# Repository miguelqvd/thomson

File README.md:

# thomson

This repo holds tools and software I write (or gather) for Thomson computers.
These were designed and built by the French company Thomson in 1982-1986, and there is a small community
of enthusisats around them.

I write tools for cross-development as well as some scene demos. There may someday be games or native tools
as well. Occasionally I hack on hardware expansions.

Be sure to visit my wiki for technical information: http://pulkomandy.tk/wiki/

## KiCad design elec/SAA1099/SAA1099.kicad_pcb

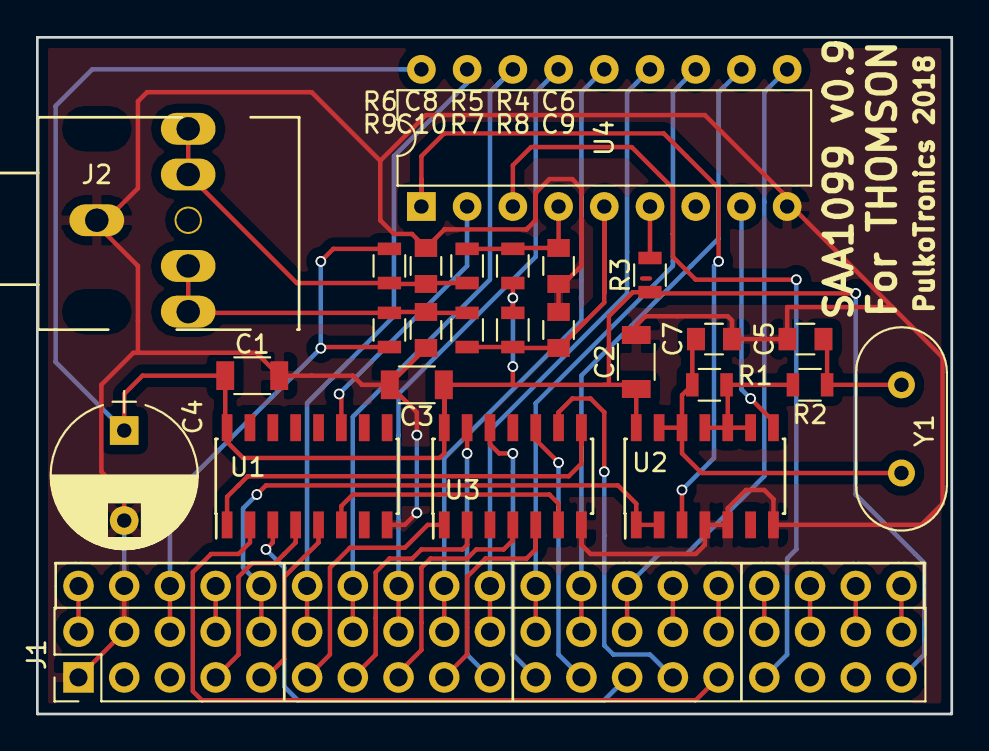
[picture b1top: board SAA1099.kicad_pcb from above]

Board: 2 copper layers, 50.8 x 37.6 mm, 26 parts (0 on the bottom side), 38 nets.

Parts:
C1, C2, C3: C; C_1206
C4: CP; CP_Radial_D8.0mm_P5.00mm
C5: 47pF; C_0805
C6, C8, C9, C10: 5nF; C_0805
C7: 33pF; C_0805
J1: Conn_02x19_Row_Letter_First; he902-he10-2x19
J2: Audio-Jack-3_2Switches; Jack_Stereo
R1: 5M; R_0805
R2: 6R; R_0805
R3, R5, R6, R8, R9: 10K; R_0805
R4, R7: 820; R_0805
U1: 74LS138; SOIC-16_3.9x9.9mm_Pitch1.27mm
U2: 74LS00; SOIC-14_3.9x8.7mm_Pitch1.27mm
U3: 74LS21; SOIC-14_3.9x8.7mm_Pitch1.27mm
U4: SAA1099; DIP-18_W7.62mm
Y1: Crystal; Crystal_HC18-U_Vertical

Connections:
//Axxx: J1.a4, U1.4
//CS: U1.11, U4.2
//WR: U2.3, U4.1
/A0: J1.a16, U4.3
/A1: J1.a15, U1.2
/A2: J1.a14, U3.9
/A3: J1.a13, U1.3
/A4: J1.a12, U3.10
/A5: J1.a11, U3.12
/A6: J1.a10, U3.13
/A7: J1.a9, U3.5
/A8: J1.a8, U3.4
/A9: J1.a7, U3.2
/A10: J1.a6, U3.1
/A11: J1.a5, U1.5
/CLK: U2.8, U4.8
/D0: J1.b13, U4.10
/D1: J1.b12, U4.11
/D2: J1.b11, U4.12
/D3: J1.b10, U4.13
/D4: J1.b9, U4.14
/D5: J1.b8, U4.15
/D6: J1.b7, U4.16
/D7: J1.b6, U4.17
/E: J1.b5, U2.1, U2.2
/Iref: R3.2, U4.6
/LINEL: C10.1, J2.2, J2.5, R8.1, R9.2
/LINER: C8.1, J2.1, J2.4, R5.1, R6.2
/OUTL: C9.1, R7.2, R8.2, U4.5
/OUTR: C6.1, R4.2, R5.2, U4.4
/SON: J1.b3, R6.1, R9.1
GND: C1.2, C2.2, C3.2, C4.2, C5.2, C6.2, C7.2, C8.2, C9.2, C10.2, J1.a1, J1.b2, J2.3, U1.8, U2.4, U2.5, U2.7, U3.7, U4.9
unnamed: C5.1, R2.1, Y1.1
unnamed: C7.1, R1.2, U2.12, U2.13, Y1.2
unnamed: R1.1, R2.2, U2.9, U2.10, U2.11
unnamed: U1.1, U3.8
unnamed: U1.6, U3.6
VCC: C1.1, C2.1, C3.1, C4.1, J1.a19, R3.1, R4.1, R7.1, U1.16, U2.14, U3.14, U4.18

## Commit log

2012-01-01 Add Memo5+.
2012-01-01 Remove useless files
2012-01-02 Add WIP HxC host software for Thomson computers. Not working yet because of timing problems...
2012-01-03 * Add re-routing of megarom (not finished!!) * Add MEMO7 connector to Thomson components library.
2012-01-04 Fix reset circuit Finish routing...
2012-01-15 Add host software for CrO2 (WIP)
2012-01-15 Load data from K7 file.
2012-01-16 Add motor on detection.
2012-01-17 * cross platform makefile * rename main file and executable
2012-01-24 WIP GUI
2012-01-24 C++ refactoring : move USB communication to device class.
2012-01-28 * Poll motor on pin status and report it in the GUI. * Some cleanup of device class.
2012-01-29 * Move GUI in its own class * Design C++ callbacksystem for IUP * Load file from menu
2012-01-29 Final version (?) of iup++, which handles callbacks with arguments. Needs C++11.
2012-02-03 Cleanup.
2012-02-04 WIP explorer * Fill in the block list * HexEditor in progress.
    Commiting because I'm trying to improve iupplusplus and want to make sure I can revert it if I fail.
2012-02-05 * Support for ZX spectrup TAP files.
2012-03-10 work in progress write support. * With latest beta firmware there is no spinup problem anymore in direct access mode, * Read the CFG file and display settings menu * Save settings (not perfectly work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
2012-03-10 More work on write support : * Avoid using the same buffer over and over again for everything, when writing this creates some problems. * Editing the configuration now works.
2012-03-16 Add PNG to MO5 converter.
2012-03-16 Add sapfs (Vital Motion modified code...)
2012-03-19 Add saptofd.
2012-03-19 GFX2MO5 * Allow picture to be less high than the screen and don't write the useless bytes * Don't set execution address to 3000, this makes no sense. Set it to 0, which makes no sense either.
2012-03-19 HxC host software : work at Forever XIII party * Switch to lwtools gcc toolchain * Fix some bugs. * Editing the HxC settings works * Selecting a floppy image works (sometimes)
2012-03-19 Add source for the Alien Message demo.
2012-03-24 Some cleanup.
2012-03-24 * Use graphical buttons for play/rec * Show error message when play fails.
2013-01-14 Port to Haiku. Untested.
2013-01-22 More work on Haiku port
2013-01-22 Fix build
2013-01-29 Add some safety checks
2013-01-30 Fix filetype detection
2013-02-10 Start to cleanup libthomson for easier reuse in upcoming projects
2013-02-12 Simple tool to wrap files in a K5 image.
2013-02-13 Make sure the last point of a GPL use the same color (FORME or FOND) as the first point of the next GPL. This avoids a glitch on the EFGJ033 gate array.
2013-02-17 Fix checksum computations
2013-03-04 Allow to use the glitched mode, sometimes it's useful.
2013-03-07 Fix path in Makefile
2013-03-07 libdemo, with stuff useful for building demos.
2013-03-07 MEA music tracker ! Very early version that won't be very useful.
2013-03-07 Allow gfx with less than 200px height. Allow to set the color for unused cells.
2013-03-09 Add binxploder, a tool to extract raw data from Thomson chunked binary files.
2013-03-17 Do not include linux specific stuff when not on linux.
2013-03-17 Work on MEATrakcer continues with some input and cursor handling.
2013-03-17 F14 - Forever young. Released at Forever 14
2013-03-26 Some fixes.
2013-03-28 Add xk5. Written by PULS but not available elsewhere on the Internet, despite the GPL licence...
2013-04-05 Add loader sourcecode.
2014-03-17 gfx2mo5: make TO mode a run-time option
    * Use getopt for parsing option.
    * The "MO5 gate array fixup" is now option -f
    * The "TO modeis now option -t
2014-08-09 Add a template for ASM projects.
    * Improvements welcome!
2014-08-09 Add that collection of 3rdparty source I had lying on my disk for some time...
2014-08-09 Add K5 file generation.
    Run it with LOADM"",,R
2014-08-09 Fix build.
2014-08-09 Add missing include.
2014-08-22 Fix filenames for windows compatibility.
2015-03-13 xk5: fix off-by-one error in snprintf length.
    * The length includes the string terminator, 8+3+1+1=13.
2015-03-13 Fix address of MEA8000.
    The TechniMusique syntetizer is a bit too forgiving in what it allows...
2015-03-13 Binxploder: split out decb handling.
    * It will soon be used in other tools.
2015-03-13 png2mo5: Add help for the options
2015-03-13 Add a version of k5towav modified for MO6.
    * Use lower WAV samplerate (smaller file)
    * Use higher speed as allowed by the MO6 (faster loading)
2015-03-15 Increase the motor off gap and add another header marker.
    * Some games have a "DCMO6" marker, identify this one as well as the others
    * When using a line in to tape adapter, the motor off doesn't work, so include an extra delay between files.
2015-03-15 Add f2k5 sourcecode.
    This is a simple tool to wrap a file with a K5 header.
2015-03-15 bastok: tool to convert a BASIC tokenized file to ASCII.
2015-03-15 Remove duplicate file
    * Same as f2k5.cpp.
2015-04-07 Add include of time.h
    * Apparently needed for some libpng versions?
2016-03-20 Add slides for my talk done at Forever 2016.
2016-03-20 binxploder: allow to list only, without dumping to file.
2016-03-20 gfx2mo5: can now convert bitmap16 files.
2016-03-20 Add documentation repository.
2018-03-21 Add a readme.
2018-03-21 HxCHost: WIP TO8 support.
    Unlikely to be finished now that SDMOTO is available, however...
2018-03-21 Add 6809 disassembler
2018-03-21 Add Foreviewer
    The tool I use (normally) to show pictures at Forever party...
2018-03-21 bastok: add test files + CoCo reference
    The CoCo has different tokens, but a similar format.
2018-03-21 bastok: add more tokens and support TO9 BASIC
2018-03-21 Add some useful docs.
2018-03-24 Add reimplementation of sd2fd and fd2sd.
    I don't want to be running Windows tools with annoying dialog boxes!
2018-05-10 SAA1099 interface for Thomson
    Untested. Working on prototype. But routing is ready...
2019-03-15 foreviewer: add bitmap 4 support
2019-03-15 binxploder: fix error handling.
    A FILE* cannot be negative.
2019-03-15 Add bitmap4 mode support
2019-03-15 Hacks to build on Haiku.
2019-03-16 Add realtime entry for Forever 2019
2019-03-16 Hacks for alien omelette
    Not working perfectly yet, to check later...
2019-03-16 Add the programming manuals for TO7 and TO8, always handy.
